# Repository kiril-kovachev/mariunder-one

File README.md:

# mariunder-one

## This repository contains project details and KICAD design files for Mariunder-one console

[Schematics files](/schematics)

[Firmware](/firmware/firmware.md)

[BOM](/bom/bom.md)

[Case](/case/case.md)

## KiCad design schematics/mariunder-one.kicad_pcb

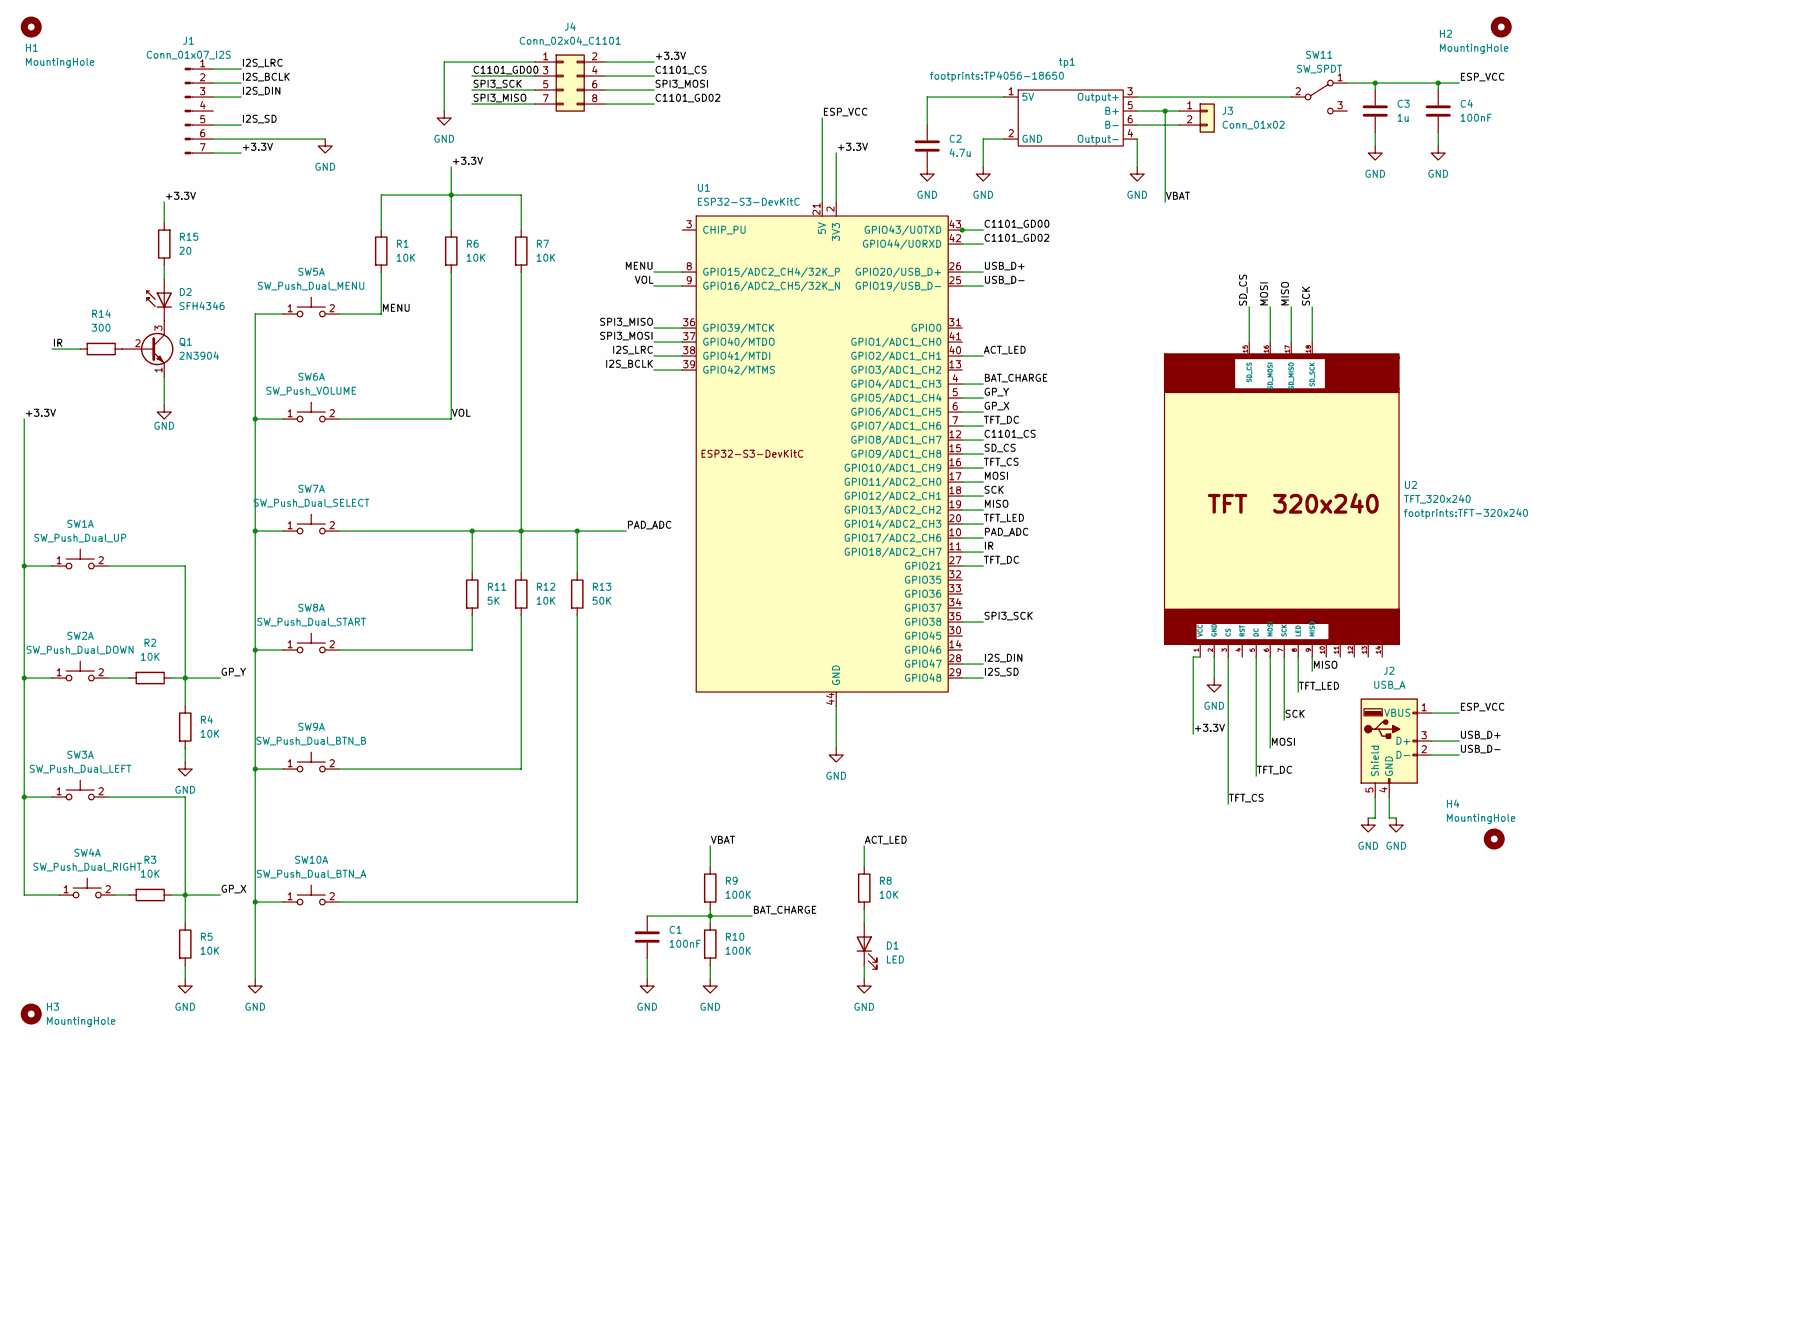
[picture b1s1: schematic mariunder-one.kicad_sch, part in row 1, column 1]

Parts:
C1, C4: 100nF; CP_Radial_D4.0mm_P2.00mm
C2: 4.7u; CP_Radial_D4.0mm_P2.00mm
C3: 1u; CP_Radial_D4.0mm_P2.00mm
D1: LED; LED_D4.0mm
D2: SFH4346; LED_D3.0mm_IRBlack
H1, H2, H3, H4: MountingHole; MountingHole_4.3mm_M4
J1: Conn_01x07_I2S; PinHeader_1x07_P2.54mm_Vertical
J2: USB_A; USB_A_Molex_67643_Horizontal
J3: Conn_01x02; PinHeader_1x02_P2.54mm_Vertical
J4: Conn_02x04_C1101; PinHeader_2x04_P2.54mm_Vertical
Q1: 2N3904; TO-92_Inline
R1, R2, R3, R4, R5, R6, R7, R8, R12: 10K; R_Axial_DIN0207_L6.3mm_D2.5mm_P7.62mm_Horizontal
R9, R10: 100K; R_Axial_DIN0207_L6.3mm_D2.5mm_P7.62mm_Horizontal
R11: 5K; R_Axial_DIN0207_L6.3mm_D2.5mm_P7.62mm_Horizontal
R13: 50K; R_Axial_DIN0207_L6.3mm_D2.5mm_P7.62mm_Horizontal
R14: 300; R_Axial_DIN0207_L6.3mm_D2.5mm_P7.62mm_Horizontal
R15: 20; R_Axial_DIN0207_L6.3mm_D2.5mm_P7.62mm_Horizontal
SW1: SW_Push_Dual_UP; SW_PUSH-12mm
SW2: SW_Push_Dual_DOWN; SW_PUSH-12mm
SW3: SW_Push_Dual_LEFT; SW_PUSH-12mm
SW4: SW_Push_Dual_RIGHT; SW_PUSH-12mm
SW5: SW_Push_Dual_MENU; SW_PUSH-12mm
SW6: SW_Push_VOLUME; SW_PUSH-12mm
SW7: SW_Push_Dual_SELECT; SW_PUSH-12mm
SW8: SW_Push_Dual_START; SW_PUSH-12mm
SW9: SW_Push_Dual_BTN_B; SW_PUSH-12mm
SW10: SW_Push_Dual_BTN_A; SW_PUSH-12mm
SW11: SW_SPDT; Switch_Angled_5mm
U1: ESP32-S3-DevKitC; ESP32-S3-DevKitC-Ali
U2: TFT_320x240; TFT-320x240
tp1: TP4056-18650

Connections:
/+3.3V: J1.7, J4.2, R1.1, R6.1, R7.1, R15.2, SW1.1 (C), SW2.1 (C), SW3.1 (C), SW4.1 (C), U1.1 (3V3), U1.2 (3V3), U2.1 (VCC)
/ACT_LED: R8.1, U1.40 (GPIO2/ADC1_CH1)
/BAT_CHARGE: C1.1, R9.2, R10.1, U1.4 (GPIO4/ADC1_CH3)
/C1101_CS: J4.4, U1.12 (GPIO8/ADC1_CH7)
/C1101_GD00: J4.3, U1.43 (GPIO43/U0TXD)
/C1101_GD02: J4.8, U1.42 (GPIO44/U0RXD)
/ESP_VCC: C3.1, C4.1, J2.1 (VBUS), SW11.1 (A), U1.21 (5V)
/GP_X: R3.1, R5.1, SW3.2 (D), U1.6 (GPIO6/ADC1_CH5)
/GP_Y: R2.1, R4.1, SW1.2 (D), U1.5 (GPIO5/ADC1_CH4)
/I2S_BCLK: J1.2, U1.39 (GPIO42/MTMS)
/I2S_DIN: J1.3, U1.28 (GPIO47)
/I2S_LRC: J1.1, U1.38 (GPIO41/MTDI)
/I2S_SD: J1.5, U1.29 (GPIO48)
/IR: R14.2, U1.11 (GPIO18/ADC2_CH7)
/MENU: R1.2, SW5.2 (D), U1.8 (GPIO15/ADC2_CH4/32K_P)
/MISO: U1.19 (GPIO13/ADC2_CH2), U2.9 (MISO), U2.17 (SD_MISO)
/MOSI: U1.17 (GPIO11/ADC2_CH0), U2.6 (MOSI), U2.16 (SD_MOSI)
/PAD_ADC: R7.2, R11.1, R12.1, R13.1, SW7.2 (D), U1.10 (GPIO17/ADC2_CH6)
/SCK: U1.18 (GPIO12/ADC2_CH1), U2.7 (SCK), U2.18 (SD_SCK)
/SD_CS: U1.15 (GPIO9/ADC1_CH8), U2.15 (SD_CS)
/SPI3_MISO: J4.7, U1.36 (GPIO39/MTCK)
/SPI3_MOSI: J4.6, U1.37 (GPIO40/MTDO)
/SPI3_SCK: J4.5, U1.35 (GPIO38)
/TFT_CS: U1.16 (GPIO10/ADC1_CH9), U2.3 (CS)
/TFT_DC: U1.7 (GPIO7/ADC1_CH6), U1.27 (GPIO21), U2.5 (DC)
/TFT_LED: U1.20 (GPIO14/ADC2_CH3), U2.8 (LED)
/USB_D+: J2.3 (D+), U1.26 (GPIO20/USB_D+)
/USB_D-: J2.2 (D-), U1.25 (GPIO19/USB_D-)
/VBAT: J3.1, R9.1, tp1.5 (B+)
/VOL: R6.2, SW6.2 (D), U1.9 (GPIO16/ADC2_CH5/32K_N)
GND: C1.2, C2.2, C3.2, C4.2, D1.1 (K), J1.6, J2.4 (GND), J2.5 (Shield), J4.1, Q1.1 (E), R4.2, R5.2, R10.2, SW5.1 (C), SW6.1 (C), SW7.1 (C), SW8.1 (C), SW9.1 (C), SW10.1 (C), U1.44 (GND), U2.2 (GND), tp1.2 (GND), tp1.4 (Output-)
unnamed: D1.2 (A), R8.2
unnamed: D2.2 (A), R15.1
unnamed: D2.1 (K), Q1.3 (C)
unnamed: J3.2, tp1.6 (B-)
unnamed: Q1.2 (B), R14.1
unnamed: R2.2, SW2.2 (D)
unnamed: R3.2, SW4.2 (D)
unnamed: R11.2, SW8.2 (D)
unnamed: R12.2, SW9.2 (D)
unnamed: R13.2, SW10.2 (D)
unnamed: SW11.2 (B), tp1.3 (Output+)
unnamed: C2.1, tp1.1 (5V)

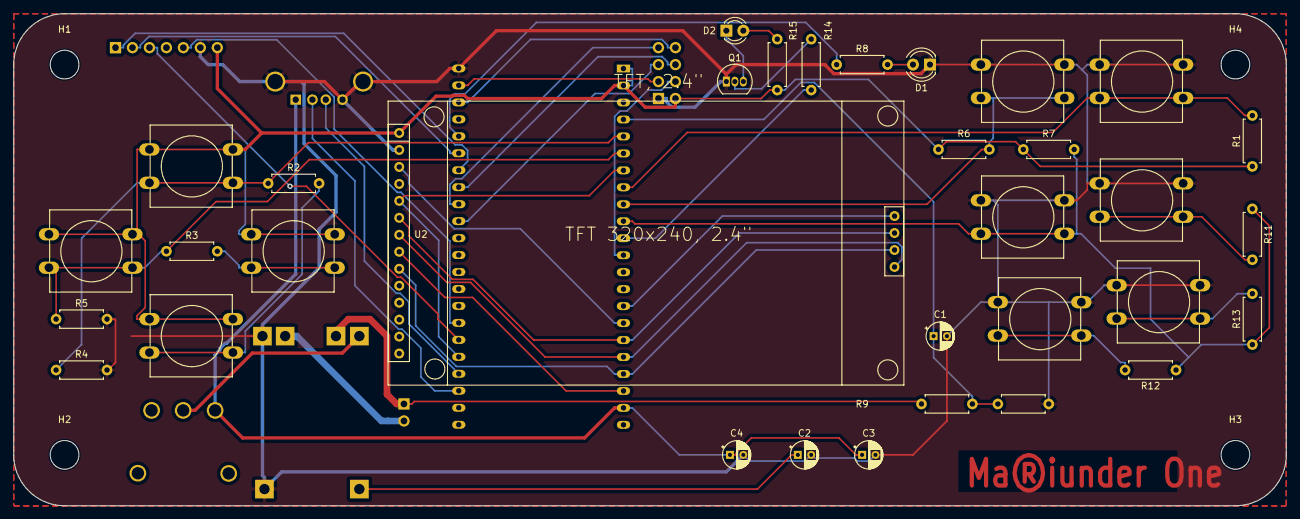
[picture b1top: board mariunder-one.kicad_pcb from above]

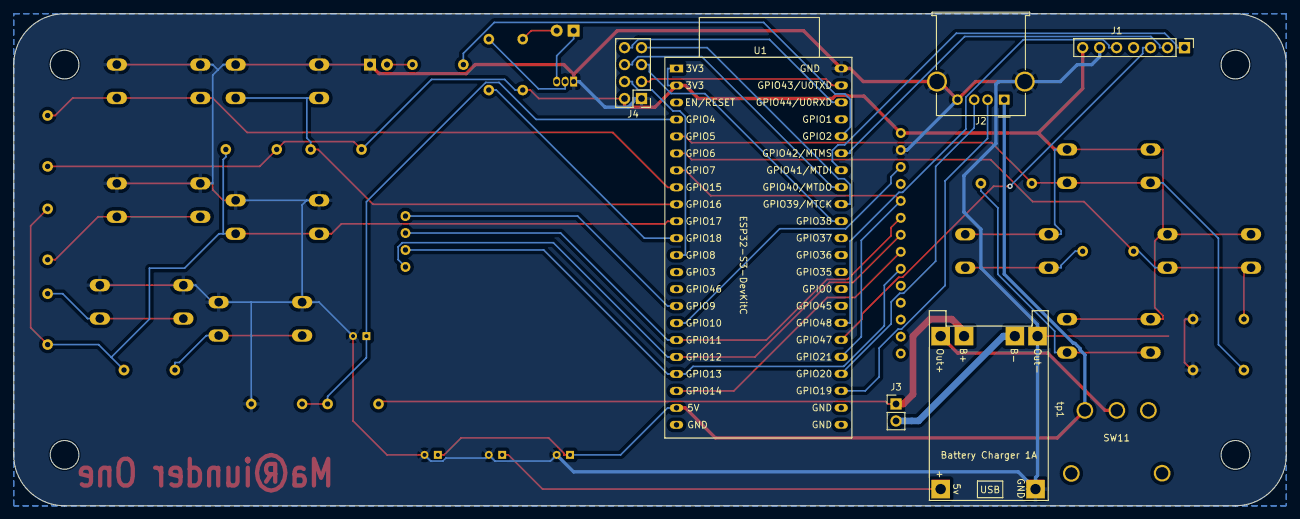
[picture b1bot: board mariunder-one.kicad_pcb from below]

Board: 2 copper layers, 190.5 x 73.7 mm, 44 parts (7 on the bottom side), 43 nets.

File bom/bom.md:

| | | | | | |
|-|-|-|-|-|-|
|1|Designator|Designation|Footprint|Quantity|Supplier and ref|
|2|R8,R12,R4,R3,R7,R1,R11,R6,R2,R5,R13|10K|R_Axial_DIN0207_L6.3mm_D2.5mm_P7.62mm_Horizontal|11| |
|3|SW1-SW11|SW_Push_Dual_UP|SW_PUSH-12mm|1| |
|4|R9,R10|100K|R_Axial_DIN0207_L6.3mm_D2.5mm_P7.62mm_Horizontal|2| |
|5|U2|TFT_320x240|TFT-320x240|1| |
|6|Q1|2N3904|TO-92_Inline|1| |
|7|C2|4.7u|CP_Radial_D4.0mm_P2.00mm|1| |
|8|D2|SFH4346|LED_D3.0mm_IRBlack|1| |
|9|C4,C1|100nF|CP_Radial_D4.0mm_P2.00mm|2| |
|10|D1|LED|LED_D4.0mm|1| |
|11|R15|20|R_Axial_DIN0207_L6.3mm_D2.5mm_P7.62mm_Horizontal|1| |
|12|C3|1u|CP_Radial_D4.0mm_P2.00mm|1| |
|13|R14|300|R_Axial_DIN0207_L6.3mm_D2.5mm_P7.62mm_Horizontal|1| |
|14|J1|MAX98357 board|PinHeader_1x07_P2.54mm_Vertical|1| |
|15|J2|USB_A connector|USB_A_Molex_67643_Horizontal|1| |
|16|tp1|TP4056 board|TP4056-18650|1| |
|17|J4|C1101 board|PinHeader_2x04_P2.54mm_Vertical|1| |
|18|J3|Battery connector|PinHeader_1x02_P2.54mm_Vertical|1| |
|19|U1|ESP32-S3-DevKitC|ESP32-S3-DevKitC-Ali|1| |

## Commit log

2023-08-08 added sch and pcb files
2023-08-08 updated project structure
2023-08-08 added kicad footprint files
2023-08-08 add firmware details
2023-09-03 Switched btn a,b, select and start to ADC2 as GPIO 35,36 and 37 are used in octal PSRAM mode
2023-09-30 added case FreeCad files and STLs
